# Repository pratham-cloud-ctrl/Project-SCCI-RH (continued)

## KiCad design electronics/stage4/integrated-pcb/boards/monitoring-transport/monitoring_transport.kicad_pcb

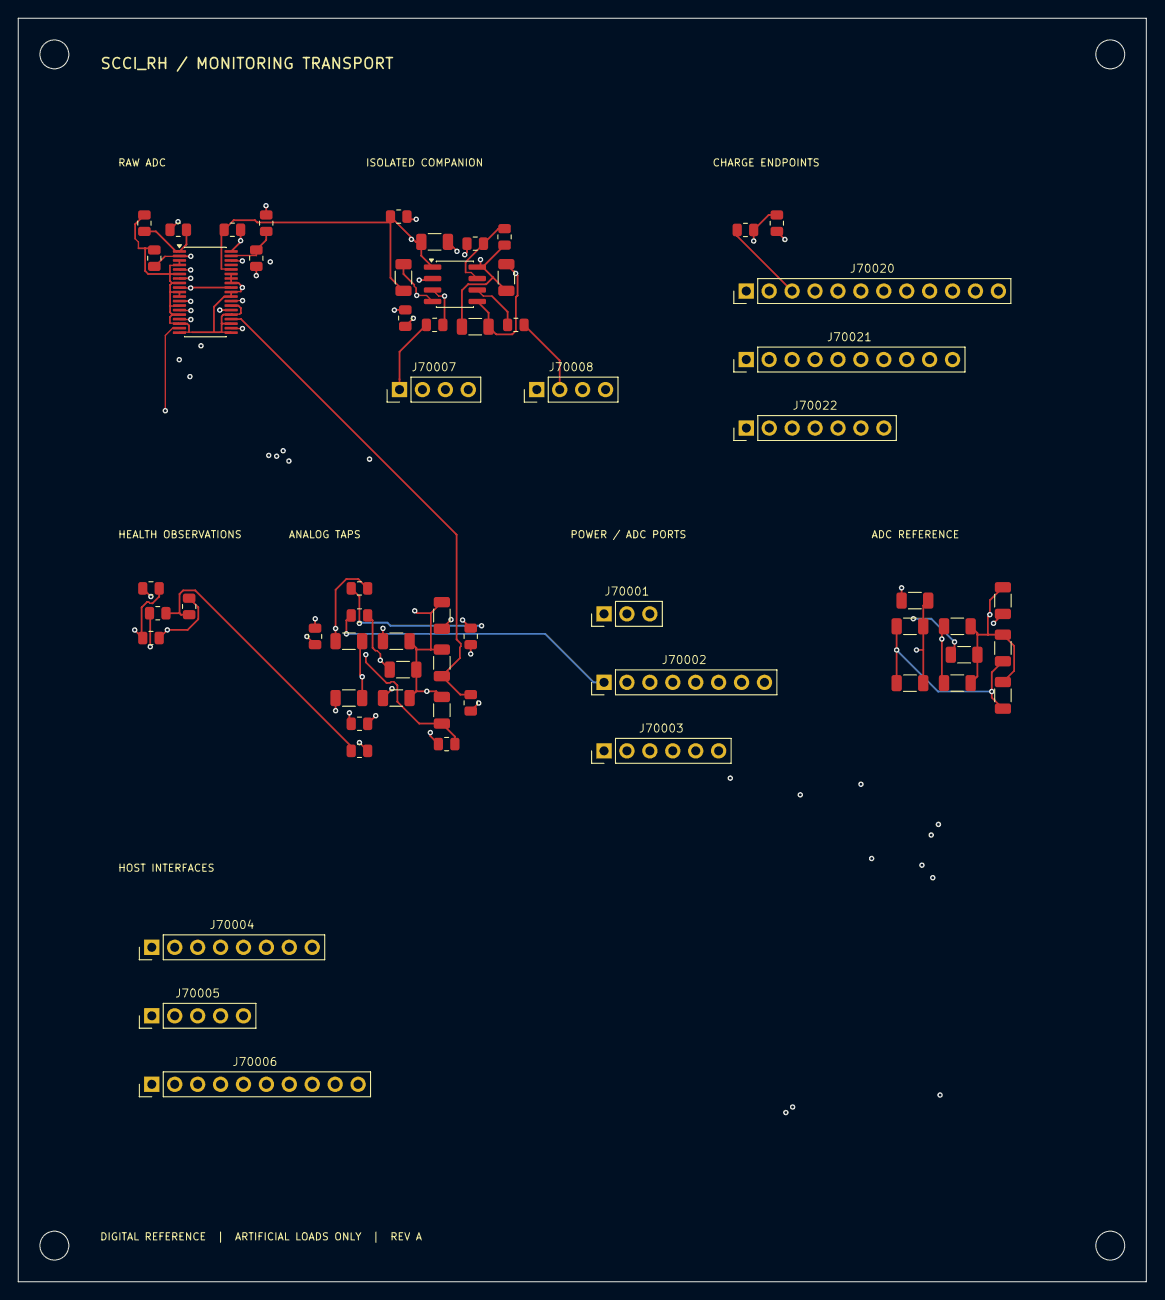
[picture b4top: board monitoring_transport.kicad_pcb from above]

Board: 4 copper layers, 125.0 x 140.0 mm, 64 parts (0 on the bottom side), 59 nets.

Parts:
C70001, C70002: 22u X7R 10V; C_1206_3216Metric
C70003, C70005, C70007, C70022, C70023: 1u X7R 10V; C_1206_3216Metric
C70004, C70006, C70008: 10u X7R 10V; C_1206_3216Metric
C70009, C70020, C70021: 100n X7R 10V; C_1206_3216Metric
C70100, C70101, C70102, C70103, C70104, C70105, C70106, C70107: 1n C0G 5%; C_1206_3216Metric
H1, H2, H3, H4: MountingHole_3.2mm_M3
J70001: HOST RAILS / RAW ADC; PinHeader_1x03_P2.54mm_Vertical
J70002: EXISTING ANALOG TAPS; PinHeader_1x08_P2.54mm_Vertical
J70003: DEDICATED RAW ADC BUS; PinHeader_1x06_P2.54mm_Vertical
J70004: TWO EXISTING CHARGE ADCs; PinHeader_1x08_P2.54mm_Vertical
J70005: CHARGE CONTROL HANDOFF; PinHeader_1x05_P2.54mm_Vertical
J70006: READ-ONLY NATIVE HEALTH; PinHeader_1x10_P2.54mm_Vertical
J70007: HOST PROCESSED UART; PinHeader_1x04_P2.54mm_Vertical
J70008: EXTERNAL COMPANION UART; PinHeader_1x04_P2.54mm_Vertical
J70020: HOST CHARGE ADC BUS; PinHeader_1x12_P2.54mm_Vertical
J70021: HOST HEALTH INPUTS; PinHeader_1x10_P2.54mm_Vertical
J70022: HOST SHARED ENDPOINT SPI; PinHeader_1x07_P2.54mm_Vertical
R70001, R70002, R70020, R70021, R70022, R70023: 33R; R_0805_2012Metric
R70003, R70004, R70005, R70006: 100k; R_0805_2012Metric
R70024, R70025: 10k; R_0805_2012Metric
R70030, R70031: 330R; R_0805_2012Metric
R70100, R70101, R70102, R70103, R70104, R70105, R70106, R70107: 100R 0.1%; R_0805_2012Metric
R70120: 4.99k 0.1%; R_0805_2012Metric
R70121: 2.49k 0.1%; R_0805_2012Metric
R70122: 2.4k 0.1%; R_0805_2012Metric
R70123: 2k 0.1%; R_0805_2012Metric
U70001: ADS8688IDBTR; TSSOP-38_4.4x9.7mm_P0.5mm
U70020: ISO6721BDR; SOIC-8_3.9x4.9mm_P1.27mm

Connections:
SYS_0d7c406c__MON_MISO: J70022.2, R70030.2, R70031.2
SYS_2d0e5b2e__CH0_QUIESCENT_OK: J70006.5, J70021.5
SYS_4f66f129__MON_VREF: J70002.5, R70104.1
SYS_5fca782c__RAW_SDO: J70003.3, U70001.36
SYS_6e45b638__HOST_UART_TX: J70007.1, R70020.1
SYS_7cf9dad5__MON_SCLK: J70004.7, J70020.7, J70022.1
SYS_20eba8c2__CH1_QUIESCENT_OK: J70006.6, J70021.6
SYS_32a601bf__MON_REARM1: J70005.4, J70020.11
SYS_36b0932b__INT_RUN1: J70005.2, J70020.9
SYS_37cfe02a__MON_VMID: J70002.6, R70105.1
SYS_40eeaa0c__CH1_VPAIR: J70002.4, R70103.1
SYS_75de6c03__RAW_RST_N: J70003.5, R70004.1, U70001.2
SYS_77c24b0d__GLOBAL_GUARD_EN: J70006.8, J70021.8
SYS_83a198be__CH0_DOUT: J70004.3, J70020.3, R70030.1
SYS_88c50083__SUP_ARMED: J70006.7, J70021.7
SYS_502efdd4__CH1_I_MON: J70002.2, R70101.1
SYS_822d2245__MON_REARM0: J70005.3, J70020.10
SYS_919c5ac8__HOST_UART_RX: J70007.2, R70021.2
SYS_37737e7c__INT_RUN0: J70005.1, J70020.8
SYS_054848d0__RAW_CS_N: J70003.4, R70003.2, U70001.38
SYS_56562df4__GND: C70001.2, C70002.2, C70003.2, C70004.2, C70005.2, C70006.2, C70007.2, C70008.2, C70009.2, C70020.2, C70022.2, C70100.2, C70101.2, C70102.2, C70103.2, C70104.2, C70105.2, C70106.2, C70107.2, J70001.3, J70002.8, J70003.6, J70004.8, J70005.5, J70006.10, J70007.4, J70020.12, J70021.10, J70022.7, R70004.2, R70005.2, R70006.2, R70121.2, R70123.2, U70001.3, U70001.4, U70001.6, U70001.8, U70001.10, U70001.11, U70001.13, U70001.15, U70001.17, U70001.19, U70001.20, U70001.22, U70001.24, U70001.26, U70001.28, U70001.29, U70001.31, U70001.32, U70001.33, U70020.4
SYS_95016e07__RAW_SCLK: J70003.1, R70002.1
SYS_98321c7b__AFE_ISOLATED_READY: J70006.4, J70021.4
SYS_08572049__HOST_3V3: C70008.1, C70009.1, C70020.1, C70022.1, J70001.2, J70007.3, R70003.1, R70024.1, U70001.34, U70020.1
SYS_66316879__RAW_SDI: J70003.2, R70001.1
SYS_93547907__RAILS_QUALIFIED: J70006.2, J70021.2
SYS_a83d484c__WATCHDOG_OK: J70006.3, J70021.3
SYS_a863a08a__CS1: J70004.5, J70020.5, J70022.6
SYS_baff84b5__CH0_VPAIR: J70002.3, R70102.1
SYS_ce0a4f53__BOTH_CNV: J70004.1, J70004.4, J70020.1, J70020.4, J70022.3, J70022.5
SYS_ce166826__HOST_5: C70004.1, C70005.1, C70006.1, C70007.1, J70001.1, R70122.1, U70001.9, U70001.30
SYS_ec2c6e7f__CS0: J70004.2, J70020.2, J70022.4
SYS_ee59c76b__PWR_FAULT_N: J70006.9, J70021.9
SYS_f8e43b73__CH0_I_MON: J70002.1, R70100.1
SYS_f199d834__PACK_BUS: J70002.7, R70120.1
SYS_fd7db492__CH1_DOUT: J70004.6, J70020.6, R70031.1
SYS_ff7fdc58__RESET_READY: J70006.1, J70021.1
monitoring-transport__ADC0: C70100.1, R70100.2, U70001.16
monitoring-transport__ADC1: C70101.1, R70101.2, U70001.18
monitoring-transport__ADC2: C70102.1, R70102.2, U70001.21
monitoring-transport__ADC3: C70103.1, R70103.2, U70001.23
monitoring-transport__ADC4: C70104.1, R70104.2, U70001.25
monitoring-transport__ADC5: C70105.1, R70105.2, U70001.27
monitoring-transport__ADC6: C70106.1, R70106.2, U70001.12
monitoring-transport__ADC7: C70107.1, R70107.2, U70001.14
monitoring-transport__COMP_3V3: C70021.1, C70023.1, J70008.3, R70025.1, U70020.8
monitoring-transport__COMP_GND: C70021.2, C70023.2, J70008.4, U70020.5
monitoring-transport__COMP_UART_RX: J70008.2, R70023.2
monitoring-transport__COMP_UART_TX: J70008.1, R70022.1
monitoring-transport__HOST5_SCALED: R70107.1, R70122.2, R70123.1
monitoring-transport__PACK_SCALED: R70106.1, R70120.2, R70121.1
monitoring-transport__RAW_REFCAP: C70002.1, C70003.1, U70001.7
monitoring-transport__RAW_REFIO: C70001.1, U70001.5
monitoring-transport__RAW_SCLK_PAD: R70002.2, R70005.1, U70001.37
monitoring-transport__RAW_SDI_PAD: R70001.2, R70006.1, U70001.1
monitoring-transport__UART_COMP_RX_PAD: R70023.1, U70020.6
monitoring-transport__UART_COMP_TX_PAD: R70022.2, R70025.2, U70020.7
monitoring-transport__UART_HOST_RX_PAD: R70021.1, U70020.2
monitoring-transport__UART_HOST_TX_PAD: R70020.2, R70024.2, U70020.3

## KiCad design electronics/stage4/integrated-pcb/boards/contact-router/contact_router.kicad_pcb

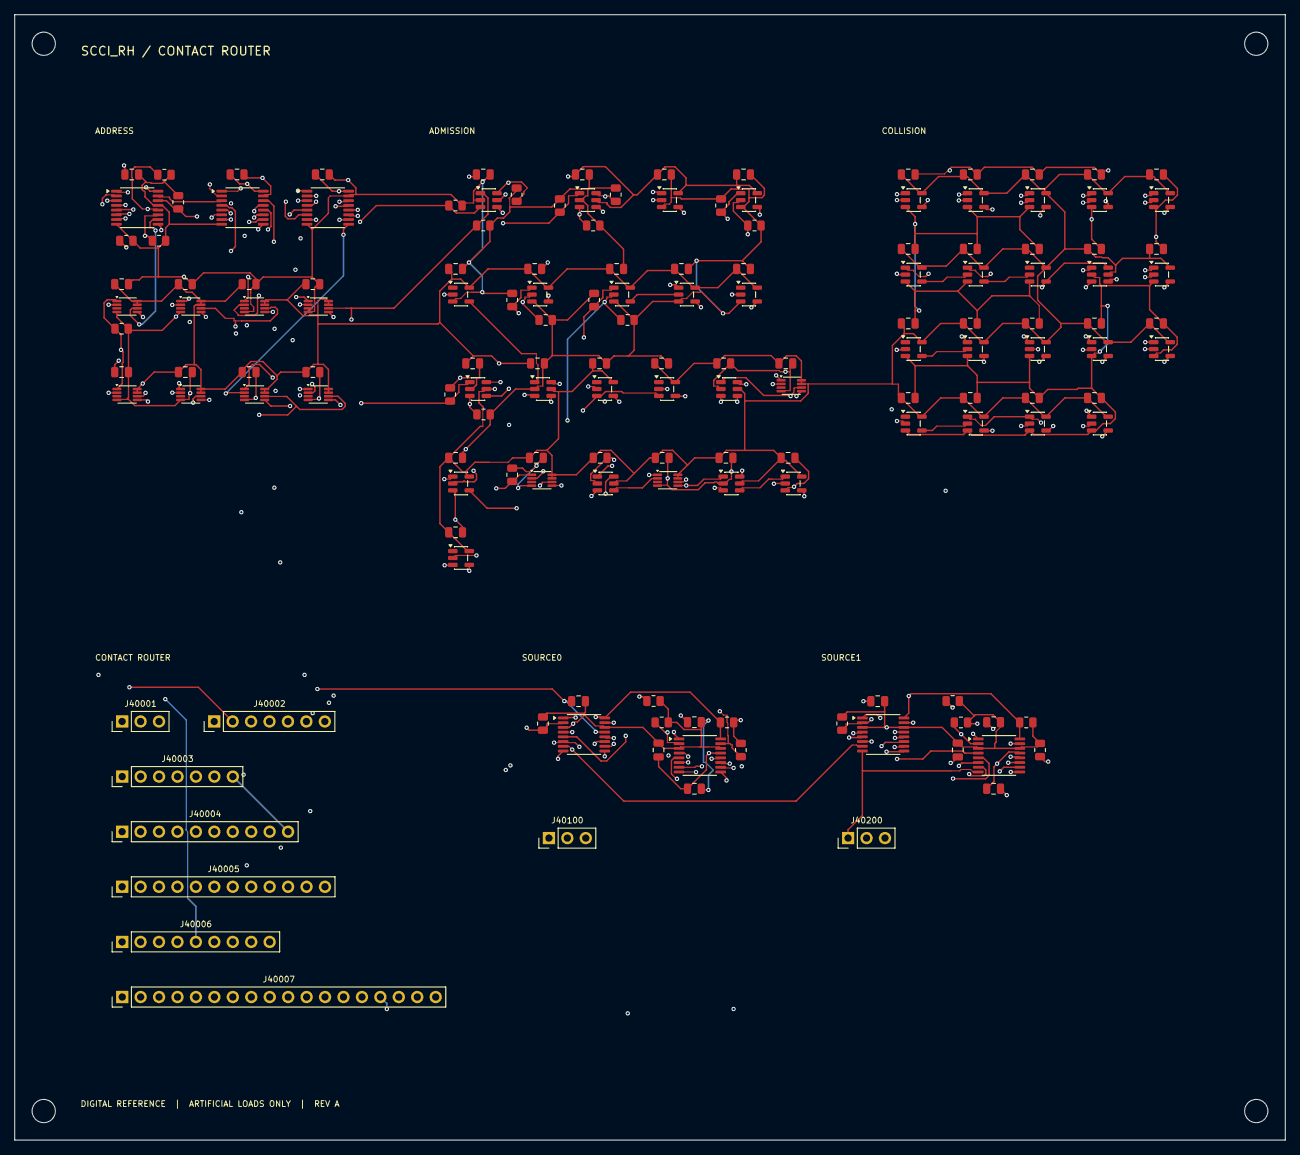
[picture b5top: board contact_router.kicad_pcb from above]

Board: 4 copper layers, 175.0 x 155.0 mm, 159 parts (0 on the bottom side), 109 nets.

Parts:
C40010, C40020, C40021, C40030, C40031, C40032, C40033, C40034, C40035, C40036, C40037, C40300, C40301, C40302, C40303, C40304, C40305, C40306, C40307, C40308, C40309, C40310, C40311, C40312, C40313, C40314, C40315, C40316, C40317, C40318, C40319, C40320, C40321, C40400, C40401, C40402, C40403, C40404, C40405, C40406, C40407, C40408, C40409, C40410, C40411, C40412, C40413, C40414, C40415, C40416, C40417, C40418: 100n X7R 10V; C_0805_2012Metric
C40100, C40101, C40200, C40201: 100n X7R 50V; C_0805_2012Metric
C40102, C40103, C40202, C40203: 1u X7R 50V; C_0805_2012Metric
H1, H2, H3, H4: MountingHole_3.2mm_M3
J40001: QUALIFIED EXTERNAL RAILS; PinHeader_1x03_P2.54mm_Vertical
J40002: CANDIDATE PRELOAD AND COMMIT; PinHeader_1x07_P2.54mm_Vertical
J40003: SOURCE ROUTE INTENT / PHASE STATUS; PinHeader_1x07_P2.54mm_Vertical
J40004: EXTERNAL OBSERVED HEALTH CONTRACTS; PinHeader_1x10_P2.54mm_Vertical
J40005: COMMAND STATUS / NOT MUX READBACK; PinHeader_1x12_P2.54mm_Vertical
J40006: ACTIVE ADDRESS BIT READBACK; PinHeader_1x09_P2.54mm_Vertical
J40007: SIXTEEN CONTACTS / TWO MONITORED RETURNS; PinHeader_1x18_P2.54mm_Vertical
J40100, J40200: DRIVER A / MONITORED RETURN; PinHeader_1x03_P2.54mm_Vertical
R40010, R40011, R40012, R40013, R40014, R40300, R40301, R40302, R40303, R40304, R40305, R40306, R40307, R40308, R40309, R40310, R40311, R40312, R40313, R40314: 10k; R_0805_2012Metric
R40100, R40101, R40102, R40103, R40104, R40200, R40201, R40202, R40203, R40204: 22k; R_0805_2012Metric
U40010: SN74LVC595APWR; TSSOP-16_4.4x5mm_P0.65mm
U40020, U40021: SN74LVC157APWR; TSSOP-16_4.4x5mm_P0.65mm
U40030, U40031, U40032, U40033, U40034, U40035, U40036, U40037, U40314, U40316, U40318: SN74LVC1G74DCUR; VSSOP-8_2.3x2mm_P0.5mm
U40100, U40101, U40200, U40201: TMUX6208PWR; TSSOP-16_4.4x5mm_P0.65mm
U40300, U40301, U40309, U40310, U40313, U40317, U40319, U40408: SN74LVC1G11DBVR; SOT-23-6
U40302, U40315, U40320, U40409, U40411, U40412, U40413, U40414, U40416, U40417, U40418: SN74LVC1G08DBVR; SOT-23-5
U40303, U40305, U40306, U40307, U40404, U40405, U40406: SN74LVC1G32DBVR; SOT-23-5
U40304, U40308, U40311, U40312, U40321, U40407, U40410, U40415: SN74LVC1G04DBVR; SOT-23-5
U40400, U40401, U40402, U40403: SN74LVC1G86DBVR; SOT-23-5

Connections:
SYS_0cbf1bda__CH1_ADDR1: J40006.6, R40203.1, U40021.5, U40035.5, U40200.16, U40201.16, U40401.2
SYS_0d1e7c21__CH0_RETURN_LOAD: J40007.17, J40100.2
SYS_1fbf7500__ROUTE_ACTIVE_BITS_VERIFIED: J40004.7, R40306.1, U40316.1
SYS_2d0e5b2e__CH0_QUIESCENT_OK: J40004.5, R40304.1, U40309.1
SYS_3ced048f__CH1_RETURN_LOAD: J40007.18, J40200.2
SYS_5aed2944__CH0_ADDR2: J40006.3, R40104.1, U40020.11, U40032.5, U40100.15, U40101.15, U40402.1
SYS_6a132103__CH1_RUN: J40003.6, R40314.1, U40306.2
SYS_6c012064__ROUTE_COMMAND_READY: J40005.1, U40320.4, U40409.1, U40413.1, U40414.1, U40418.1
SYS_6d4bb3d1__STIM11_CONTACT: J40007.12, U40101.7, U40201.7
SYS_8b50701c__STIM01_CONTACT: J40007.2, U40100.5, U40200.5
SYS_08e41150__CH0_ADDR1: J40006.2, R40103.1, U40020.5, U40031.5, U40100.16, U40101.16, U40401.1
SYS_11f4403a__ROUTE_SER: J40002.1, R40010.1, U40010.14
SYS_20eba8c2__CH1_QUIESCENT_OK: J40004.6, R40305.1, U40309.3
SYS_32f1b236__STIM12_CONTACT: J40007.13, U40101.12, U40201.12
SYS_36b8c84f__STIM02_CONTACT: J40007.3, U40100.6, U40200.6
SYS_46ea5f03__CH0_REQUEST: J40003.3, R40311.1, U40305.1
SYS_56ebc071__CH0_MON_PERMIT: J40004.8, R40307.1, U40301.3
SYS_74b9e55a__STIM10_CONTACT: J40007.11, U40101.6, U40201.6
SYS_83ddb634__CH1_WANT_ROUTE: J40003.2, R40310.1, U40303.2, U40408.3, U40414.2, U40418.2
SYS_84f28705__CH1_ROUTE_LOCKED: J40005.8, U40418.4
SYS_126bf237__STIM14_CONTACT: J40007.15, U40101.10, U40201.10
SYS_223a43dd__STIM03_CONTACT: J40007.4, U40100.7, U40200.7
SYS_401be33b__CH1_A_ROUTER: J40200.1, U40200.8, U40201.8
SYS_695f3a7c__CH0_RUN: J40003.5, R40313.1, U40306.1
SYS_917b1360__CH0_A_ROUTER: J40100.1, U40100.8, U40101.8
SYS_15689dc4__VH_24: C40100.1, C40101.1, C40102.1, C40103.1, C40200.1, C40201.1, C40202.1, C40203.1, J40001.1, U40100.13, U40101.13, U40200.13, U40201.13
SYS_56562df4__GND: C40010.2, C40020.2, C40021.2, C40030.2, C40031.2, C40032.2, C40033.2, C40034.2, C40035.2, C40036.2, C40037.2, C40100.2, C40101.2, C40102.2, C40103.2, C40200.2, C40201.2, C40202.2, C40203.2, C40300.2, C40301.2, C40302.2, C40303.2, C40304.2, C40305.2, C40306.2, C40307.2, C40308.2, C40309.2, C40310.2, C40311.2, C40312.2, C40313.2, C40314.2, C40315.2, C40316.2, C40317.2, C40318.2, C40319.2, C40320.2, C40321.2, C40400.2, C40401.2, C40402.2, C40403.2, C40404.2, C40405.2, C40406.2, C40407.2, C40408.2, C40409.2, C40410.2, C40411.2, C40412.2, C40413.2, C40414.2, C40415.2, C40416.2, C40417.2, C40418.2, J40001.3, J40002.7, J40003.7, J40004.10, J40005.12, J40006.9, J40100.3, J40200.3, R40010.2, R40011.2, R40012.2, R40013.2, R40014.2, R40100.2, R40101.2, R40102.2, R40103.2, R40104.2, R40200.2, R40201.2, R40202.2, R40203.2, R40204.2, R40300.2, R40301.2, R40302.2, R40303.2, R40304.2, R40305.2, R40306.2, R40307.2, R40308.2, R40309.2, R40310.2, R40311.2, R40312.2, R40313.2, R40314.2, U40010.8, U40010.13, U40020.8, U40020.15, U40021.8, U40021.15, U40030.4, U40031.4, U40032.4, U40033.4, U40034.4, U40035.4, U40036.4, U40037.4, U40100.3, U40100.14, U40101.3, U40101.14, U40200.3, U40200.14, U40201.3, U40201.14, U40300.2, U40301.2, U40302.3, U40303.3, U40304.3, U40305.3, U40306.3, U40307.3, U40308.3, U40309.2, U40310.2, U40311.3, U40312.3, U40313.2, U40314.4, U40315.3, U40316.4, U40317.2, U40318.4, U40319.2, U40320.3, U40321.3, U40400.3, U40401.3, U40402.3, U40403.3, U40404.3, U40405.3, U40406.3, U40407.3, U40408.2, U40409.3, U40410.3, U40411.3, U40412.3, U40413.3, U40414.3, U40415.3, U40416.3, U40417.3, U40418.3
SYS_80673a9e__STIM08_CONTACT: J40007.9, U40101.4, U40201.4
SYS_82867ca5__STIM00_CONTACT: J40007.1, U40100.4, U40200.4
SYS_087068cd__CH0_ADDR0: J40006.1, R40102.1, U40020.2, U40030.5, U40100.1, U40101.1, U40400.1
SYS_98321c7b__AFE_ISOLATED_READY: J40004.4, R40303.1, U40301.1
SYS_344482b2__STIM13_CONTACT: J40007.14, U40101.11, U40201.11
SYS_1954027d__CH0_ROUTE_LOCKED: J40005.7, U40413.4
SYS_08572049__HOST_3V3: C40010.1, C40020.1, C40021.1, C40030.1, C40031.1, C40032.1, C40033.1, C40034.1, C40035.1, C40036.1, C40037.1, C40300.1, C40301.1, C40302.1, C40303.1, C40304.1, C40305.1, C40306.1, C40307.1, C40308.1, C40309.1, C40310.1, C40311.1, C40312.1, C40313.1, C40314.1, C40315.1, C40316.1, C40317.1, C40318.1, C40319.1, C40320.1, C40321.1, C40400.1, C40401.1, C40402.1, C40403.1, C40404.1, C40405.1, C40406.1, C40407.1, C40408.1, C40409.1, C40410.1, C40411.1, C40412.1, C40413.1, C40414.1, C40415.1, C40416.1, C40417.1, C40418.1, J40001.2, U40010.16, U40020.16, U40021.16, U40030.7, U40030.8, U40031.7, U40031.8, U40032.7, U40032.8, U40033.7, U40033.8, U40034.7, U40034.8, U40035.7, U40035.8, U40036.7, U40036.8, U40037.7, U40037.8, U40300.5, U40301.5, U40302.5, U40303.5, U40304.5, U40305.5, U40306.5, U40307.5, U40308.5, U40309.5, U40310.5, U40311.5, U40312.5, U40313.5, U40314.7, U40314.8, U40315.5, U40316.7, U40316.8, U40317.5, U40318.7, U40318.8, U40319.5, U40320.5, U40321.5, U40400.5, U40401.5, U40402.5, U40403.5, U40404.5, U40405.5, U40406.5, U40407.5, U40408.5, U40409.5, U40410.5, U40411.5, U40412.5, U40413.5, U40414.5, U40415.5, U40416.5, U40417.5, U40418.5
SYS_93547907__RAILS_QUALIFIED: J40004.2, R40301.1, U40300.3
SYS_a83d484c__WATCHDOG_OK: J40004.3, R40302.1, U40300.6
SYS_aa321af6__CH1_MON_PERMIT: J40004.9, R40308.1, U40301.6
SYS_b6a3943c__ROUTE_COMMIT: J40002.4, R40013.1, U40030.1, U40031.1, U40032.1, U40033.1, U40034.1, U40035.1, U40036.1, U40037.1, U40311.2, U40314.1
SYS_b6ef4aed__CH1_ADDR3: J40006.8, U40021.14, U40037.5, U40403.2, U40415.2, U40417.2
SYS_b675ff0d__STIM06_CONTACT: J40007.7, U40100.10, U40200.10
SYS_c3abe6bc__CH1_ADDR0: J40006.5, R40202.1, U40021.2, U40034.5, U40200.1, U40201.1, U40400.2
SYS_cf17d7c4__STIM07_CONTACT: J40007.8, U40100.9, U40200.9
SYS_d5e1f64a__ROUTE_SRCLK: J40002.2, R40011.1, U40010.11
SYS_dcbe1273__STIM04_CONTACT: J40007.5, U40100.12, U40200.12
SYS_dd388269__CH1_REQUEST: J40003.4, R40312.1, U40305.2
SYS_e338b670__CH0_WANT_ROUTE: J40003.1, R40309.1, U40303.1, U40408.1, U40409.2, U40413.2
SYS_eb2c0acf__STIM09_CONTACT: J40007.10, U40101.5, U40201.5
SYS_ed4497b7__ROUTE_REARM: J40002.5, R40014.1, U40318.1
SYS_f00e6304__STIM15_CONTACT: J40007.16, U40101.9, U40201.9
SYS_f373e353__CH1_ADDR2: J40006.7, R40204.1, U40021.11, U40036.5, U40200.15, U40201.15, U40402.2
SYS_f7756399__CH0_ADDR3: J40006.4, U40020.14, U40033.5, U40403.1, U40410.2, U40412.2
SYS_fa6c9e06__STIM05_CONTACT: J40007.6, U40100.11, U40200.11
SYS_fd131f77__ROUTE_PRELOAD_LATCH: J40002.3, R40012.1, U40010.12
SYS_ff7fdc58__RESET_READY: J40004.1, R40300.1, U40010.10, U40030.6, U40031.6, U40032.6, U40033.6, U40034.6, U40035.6, U40036.6, U40037.6, U40300.1
contact-router__ACK_CLR_N: U40315.4, U40316.6
contact-router__ADDR_ANY_DIFF: U40406.4, U40407.2
contact-router__ADDR_DIFF0: U40400.4, U40404.1
contact-router__ADDR_DIFF1: U40401.4, U40404.2
contact-router__ADDR_DIFF2: U40402.4, U40405.1
contact-router__ADDR_DIFF3: U40403.4, U40405.2
contact-router__ADDR_DIFF_HI: U40405.4, U40406.2
contact-router__ADDR_DIFF_LO: U40404.4, U40406.1
contact-router__ANY_PHASE: U40307.4, U40308.2
contact-router__ANY_REQUEST: U40305.4, U40307.1
contact-router__ANY_RUN: U40306.4, U40307.2
contact-router__ANY_WANT: U40303.4, U40304.2
contact-router__BASE_HEALTH: U40302.4, U40309.6, U40313.1, U40314.6, U40315.1, U40319.3
contact-router__CH0_ADDR_D0: U40020.4, U40030.2
contact-router__CH0_ADDR_D1: U40020.7, U40031.2
contact-router__CH0_ADDR_D2: U40020.9, U40032.2
contact-router__CH0_ADDR_D3: U40020.12, U40033.2
contact-router__CH0_BANK0_EN: R40100.1, U40100.2, U40411.4
contact-router__CH0_BANK0_SELECT: U40410.4, U40411.2
contact-router__CH0_BANK1_EN: R40101.1, U40101.2, U40412.4
contact-router__CH0_PENDING0: U40010.15, U40020.3
contact-router__CH0_PENDING1: U40010.1, U40020.6
contact-router__CH0_PENDING2: U40010.2, U40020.10
contact-router__CH0_PENDING3: U40010.3, U40020.13
contact-router__CH0_ROUTE_EN: J40005.5, U40409.4, U40411.1, U40412.1
contact-router__CH1_ADDR_D0: U40021.4, U40034.2
contact-router__CH1_ADDR_D1: U40021.7, U40035.2
contact-router__CH1_ADDR_D2: U40021.9, U40036.2
contact-router__CH1_ADDR_D3: U40021.12, U40037.2
contact-router__CH1_BANK0_EN: R40200.1, U40200.2, U40416.4
contact-router__CH1_BANK0_SELECT: U40415.4, U40416.2
contact-router__CH1_BANK1_EN: R40201.1, U40201.2, U40417.4
contact-router__CH1_PENDING0: U40010.4, U40021.3
contact-router__CH1_PENDING1: U40010.5, U40021.6
contact-router__CH1_PENDING2: U40010.6, U40021.10
contact-router__CH1_PENDING3: U40010.7, U40021.13
contact-router__CH1_ROUTE_EN: J40005.6, U40414.4, U40416.1, U40417.1
contact-router__COMMIT_N: U40311.4, U40313.3, U40315.2, U40319.6
contact-router__COMMIT_SEEN: J40005.11, U40314.5, U40316.2, U40317.1
contact-router__HEALTH_A: U40300.4, U40302.1
contact-router__HEALTH_B: U40301.4, U40302.2
contact-router__NO_CONFLICT: U40312.4, U40313.6, U40320.2
contact-router__NO_PHASE: U40308.4, U40310.3
contact-router__NO_WANT: U40304.4, U40310.1
contact-router__QUIET_HEALTH: U40309.4, U40310.6
contact-router__QUIET_SAFE: J40005.9, U40020.1, U40021.1, U40310.4, U40314.2, U40317.3
contact-router__READBACK_SEEN: J40005.10, U40316.5, U40317.6
contact-router__READY_A: U40319.4, U40320.1
contact-router__REARM_D: U40317.4, U40318.2
contact-router__ROUTE_ADDR_EQUAL: J40005.3, U40407.4, U40408.6
contact-router__ROUTE_BLOCK: J40005.2, U40321.4
contact-router__ROUTE_CONFLICT: J40005.4, U40312.2, U40408.4
contact-router__ROUTE_SHIFT_TAIL: J40002.6, U40010.9
contact-router__ROUTE_VALID: U40318.5, U40319.1, U40321.2
contact-router__VALID_CLR_N: U40313.4, U40318.6

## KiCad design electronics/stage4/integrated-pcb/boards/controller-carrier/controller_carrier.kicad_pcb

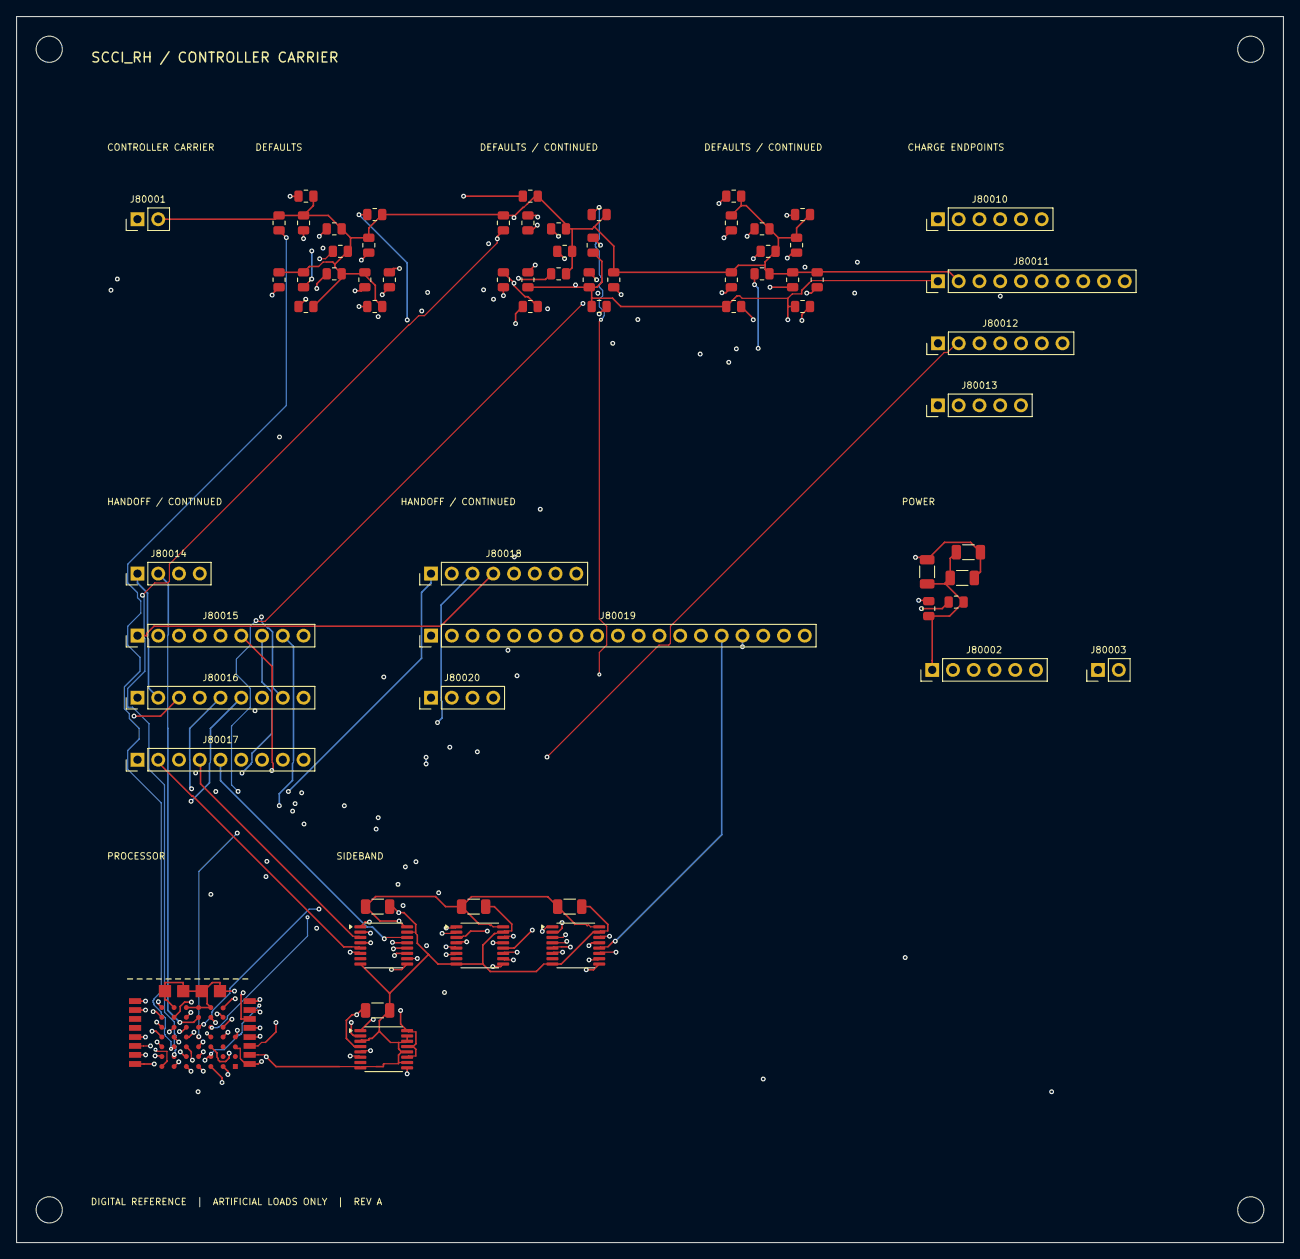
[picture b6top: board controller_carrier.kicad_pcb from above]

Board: 4 copper layers, 155.0 x 150.0 mm, 72 parts (0 on the bottom side), 81 nets.

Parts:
C80001: 47u X7R 10V; C_1206_3216Metric
C80002: 1u X7R 10V; C_1206_3216Metric
C80003, C80010, C80011, C80012, C80013: 100n X7R 10V; C_1206_3216Metric
H1, H2, H3, H4: MountingHole_3.2mm_M3
J80001: HOST POWER; PinHeader_1x02_P2.54mm_Vertical
J80002: SWD / TARGET VREF; PinHeader_1x06_P2.54mm_Vertical
J80003: RESET SHORTING HEADER; PinHeader_1x02_P2.54mm_Vertical
J80010: RAW MONITOR; PinHeader_1x06_P2.54mm_Vertical
J80011: ISOLATED RECORDING HOST; PinHeader_1x10_P2.54mm_Vertical
J80012: SHARED CHARGE ENDPOINT SPI; PinHeader_1x07_P2.54mm_Vertical
J80013: DOSE / MONITOR REARM; PinHeader_1x05_P2.54mm_Vertical
J80014: DAC SERIAL; PinHeader_1x04_P2.54mm_Vertical
J80015: DRIVER REQUEST / POLARITY; PinHeader_1x09_P2.54mm_Vertical
J80016: ROUTE CANDIDATE / COMMIT; PinHeader_1x09_P2.54mm_Vertical
J80017: ACTIVE ROUTE READBACK; PinHeader_1x09_P2.54mm_Vertical
J80018: SUPERVISION CONTROL; PinHeader_1x08_P2.54mm_Vertical
J80019: NATIVE HEALTH OBSERVATIONS; PinHeader_1x19_P2.54mm_Vertical
J80020: ISOLATED COMPANION HOST UART; PinHeader_1x04_P2.54mm_Vertical
R80001: 0R; R_0805_2012Metric
R80002, R80100, R80101, R80102, R80103, R80104, R80105, R80106, R80107, R80108, R80109, R80110, R80111, R80112, R80113, R80114, R80115, R80116, R80117, R80118, R80119, R80120, R80121, R80122, R80123, R80124, R80125, R80126, R80127, R80128, R80129, R80130, R80131, R80132, R80133, R80134, R80135, R80136, R80137, R80138, R80139: 10k; R_0805_2012Metric
U80001: FANSTEL BT40F / nRF5340; BT40F_Manufacturer_66Pad
U80010, U80011, U80012, U80013: SN74LVC165APWR; TSSOP-16_4.4x5mm_P0.65mm

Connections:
SYS_0cbf1bda__CH1_ADDR1: J80017.6, U80010.13
SYS_0d7c406c__MON_MISO: J80012.2, U80001.C2
SYS_1fbf7500__ROUTE_ACTIVE_BITS_VERIFIED: J80016.6, R80103.1, U80001.6
SYS_2d0e5b2e__CH0_QUIESCENT_OK: J80019.5, U80011.14
SYS_3abe1caf__BOTH_DRV_REARM: J80015.4, J80015.8, R80132.1, U80001.E2
SYS_3b27d056__MINUS0: J80015.3, R80129.1, U80001.2
SYS_4d4028f1__AFE_MOSI: J80011.4, R80111.1, U80001.B3
SYS_4dbe75ce__AFE_MISO: J80011.6, U80001.B4
SYS_5aed2944__CH0_ADDR2: J80017.3, U80010.4
SYS_5fca782c__RAW_SDO: J80010.3, U80001.E6
SYS_6a132103__CH1_RUN: J80019.13, U80012.14
SYS_6c012064__ROUTE_COMMAND_READY: J80019.16, U80012.11
SYS_6e45b638__HOST_UART_TX: J80020.1, R80138.2, U80001.Z3
SYS_7cf9dad5__MON_SCLK: J80012.1, R80115.1, U80001.C5
SYS_7db86ec0__PHASE_REARM0: J80018.6, R80136.1, U80001.Z1
SYS_8b29b23f__AFE_CONNECT: J80011.7, R80113.1, U80001.B2
SYS_08e41150__CH0_ADDR1: J80017.2, U80010.5
SYS_9c8a42b1__CH1_TIMEOUT: J80019.18, U80013.5
SYS_11f4403a__ROUTE_SER: J80014.3, J80016.1, R80124.1, U80001.13
SYS_18e49fe8__AFE_CS_ASSERT: J80011.5, R80112.1, U80001.A4
SYS_20eba8c2__CH1_QUIESCENT_OK: J80019.6, U80011.13
SYS_32a601bf__MON_REARM1: J80013.4, R80122.1, U80001.D3
SYS_36b0932b__INT_RUN1: J80013.2, R80120.2, U80001.D1
SYS_46e29157__PHASE_REARM1: J80018.7, R80137.1, U80001.Z2
SYS_46ea5f03__CH0_REQUEST: J80015.1, J80018.4, R80126.1, U80001.A5
SYS_54dd20d7__CH0_TIMEOUT: J80019.17, U80013.6
SYS_56ebc071__CH0_MON_PERMIT: J80019.7, U80011.12
SYS_75de6c03__RAW_RST_N: J80010.5, R80109.1, U80001.B5
SYS_77c24b0d__GLOBAL_GUARD_EN: J80019.11, U80012.4
SYS_83ddb634__CH1_WANT_ROUTE: J80016.8, R80105.1, U80001.A2
SYS_88c50083__SUP_ARMED: J80019.10, U80012.5
SYS_628d7747__PLUS1: J80015.6, R80130.1, U80001.E0
SYS_695f3a7c__CH0_RUN: J80019.12, U80012.3
SYS_822d2245__MON_REARM0: J80013.3, R80121.1, U80001.D2
SYS_919c5ac8__HOST_UART_RX: J80020.2, U80001.Z4
SYS_973f460c__PLUS0: J80015.2, R80128.1, U80001.1
SYS_37737e7c__INT_RUN0: J80013.1, R80119.2, U80001.C6
SYS_054848d0__RAW_CS_N: J80010.4, R80108.2, U80001.12
SYS_56562df4__GND: C80001.2, C80002.2, C80003.2, C80010.2, C80011.2, C80012.2, C80013.2, J80001.2, J80002.3, J80002.6, J80003.2, J80010.6, J80011.2, J80011.10, J80012.7, J80013.5, J80014.4, J80015.9, J80016.9, J80017.9, J80018.8, J80019.19, J80020.4, R80100.2, R80101.2, R80102.2, R80103.2, R80104.2, R80105.2, R80106.2, R80107.2, R80109.2, R80110.2, R80111.2, R80112.2, R80113.2, R80114.2, R80115.2, R80116.2, R80121.2, R80122.2, R80123.2, R80124.2, R80126.2, R80127.2, R80128.2, R80129.2, R80130.2, R80131.2, R80132.2, R80133.2, R80134.2, R80135.2, R80136.2, R80137.2, U80001.10, U80001.A0, U80001.B0, U80001.C0, U80001.D0, U80001.H0, U80001.H1, U80001.H2, U80001.H3, U80010.8, U80010.15, U80011.8, U80011.15, U80012.8, U80012.15, U80013.3, U80013.8, U80013.10, U80013.12, U80013.14, U80013.15
SYS_087068cd__CH0_ADDR0: J80017.1, U80010.6
SYS_95016e07__RAW_SCLK: J80010.1, R80106.1, U80001.A3
SYS_98321c7b__AFE_ISOLATED_READY: J80019.4, U80011.3
SYS_08572049__HOST_3V3: C80010.1, C80011.1, C80012.1, C80013.1, J80001.1, J80011.1, J80020.3, R80001.1, R80108.1, R80117.1, R80118.1, R80119.1, R80120.1, R80125.1, R80138.1, R80139.1, U80010.16, U80011.16, U80012.16, U80013.4, U80013.11, U80013.13, U80013.16
SYS_66316879__RAW_SDI: J80010.2, R80107.1, U80001.11
SYS_82531809__FAULT_RESET: J80018.2, R80134.1, U80001.A6
SYS_93547907__RAILS_QUALIFIED: J80019.2, U80011.5
SYS_a83d484c__WATCHDOG_OK: J80019.3, U80011.4
SYS_a863a08a__CS1: J80012.6, R80118.2, U80001.C3
SYS_a9673f8c__AFE_RECORD: J80011.8, R80114.1, U80001.F3
SYS_aa321af6__CH1_MON_PERMIT: J80019.8, U80011.11
SYS_b6a3943c__ROUTE_COMMIT: J80016.4, R80101.1, U80001.8
SYS_b6ef4aed__CH1_ADDR3: J80017.8, U80010.11
SYS_bb444a6e__SUP_REARM: J80018.1, R80133.1, U80001.E3
SYS_c3abe6bc__CH1_ADDR0: J80017.5, U80010.14
SYS_c659d53f__CH1_TIMER: J80019.15, U80012.12
SYS_ca7ea3db__CH0_TIMER: J80019.14, U80012.13
SYS_ce0a4f53__BOTH_CNV: J80012.3, J80012.5, R80116.1, U80001.D5
SYS_ce1178b4__AFE_FAULT_N: J80011.9, U80001.B1
SYS_d5e1f64a__ROUTE_SRCLK: J80014.1, J80016.2, R80123.1, U80001.D4, U80010.2, U80011.2, U80012.2, U80013.2
SYS_dd388269__CH1_REQUEST: J80015.5, J80018.5, R80127.1, U80001.D6
SYS_e3faaec0__WDI: J80018.3, R80135.1, U80001.Z0
SYS_e338b670__CH0_WANT_ROUTE: J80016.7, R80104.1, U80001.A1
SYS_e496c0b2__DAC_SYNC_N: J80014.2, R80125.2, U80001.C1
SYS_ec2c6e7f__CS0: J80012.4, R80117.2, U80001.C4
SYS_ed4497b7__ROUTE_REARM: J80016.5, R80102.1, U80001.5
SYS_edc800df__MINUS1: J80015.7, R80131.1, U80001.E1
SYS_ee59c76b__PWR_FAULT_N: J80019.9, U80012.6
SYS_f30c60de__AFE_SCLK: J80011.3, R80110.1, U80001.B6
SYS_f373e353__CH1_ADDR2: J80017.7, U80010.12
SYS_f7756399__CH0_ADDR3: J80017.4, U80010.3
SYS_fd131f77__ROUTE_PRELOAD_LATCH: J80016.3, R80100.1, U80001.7
SYS_ff7fdc58__RESET_READY: J80019.1, U80011.6
controller-carrier__MCU_3V3: C80001.1, C80002.1, C80003.1, J80002.1, R80001.2, R80002.1, U80001.9, U80001.F4
controller-carrier__MCU_RESET_N: J80002.5, J80003.1, R80002.2, U80001.14
controller-carrier__SB_Q1: U80010.10, U80011.9
controller-carrier__SB_Q2: U80011.10, U80012.9
controller-carrier__SB_Q3: U80012.10, U80013.9
controller-carrier__SIDEBAND_DATA: U80001.Z6, U80010.9
controller-carrier__SIDEBAND_LOAD_N: R80139.2, U80001.Z5, U80010.1, U80011.1, U80012.1, U80013.1
controller-carrier__SWCLK: J80002.4, U80001.15
controller-carrier__SWDIO: J80002.2, U80001.16
